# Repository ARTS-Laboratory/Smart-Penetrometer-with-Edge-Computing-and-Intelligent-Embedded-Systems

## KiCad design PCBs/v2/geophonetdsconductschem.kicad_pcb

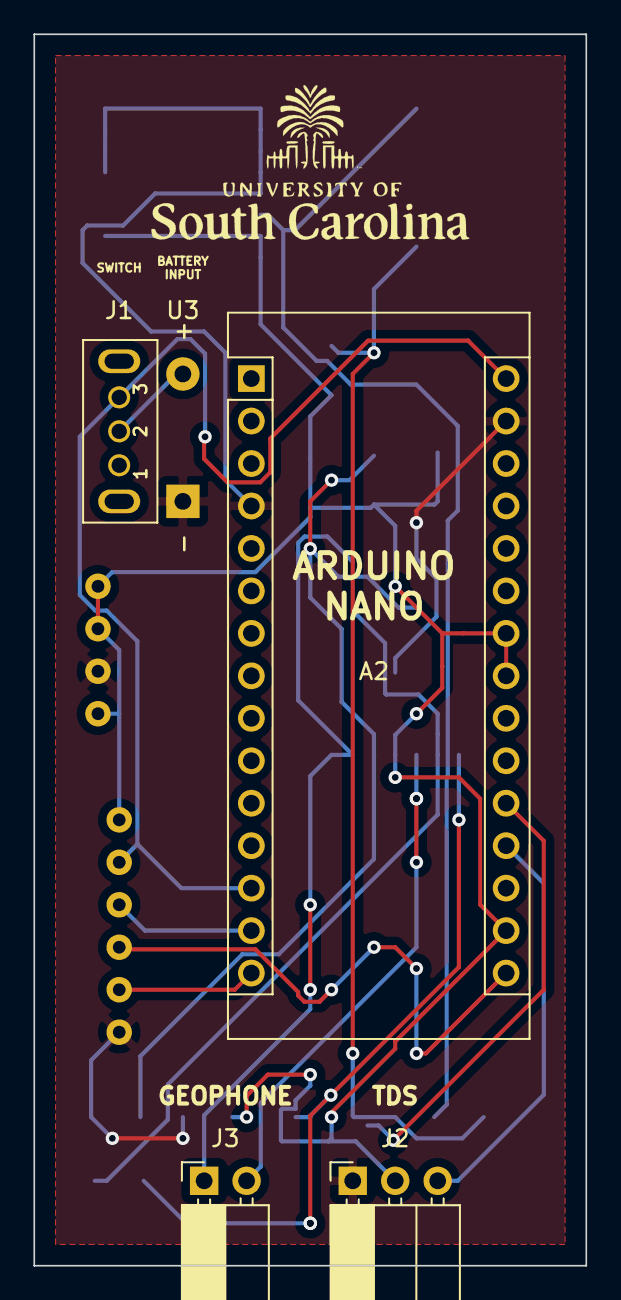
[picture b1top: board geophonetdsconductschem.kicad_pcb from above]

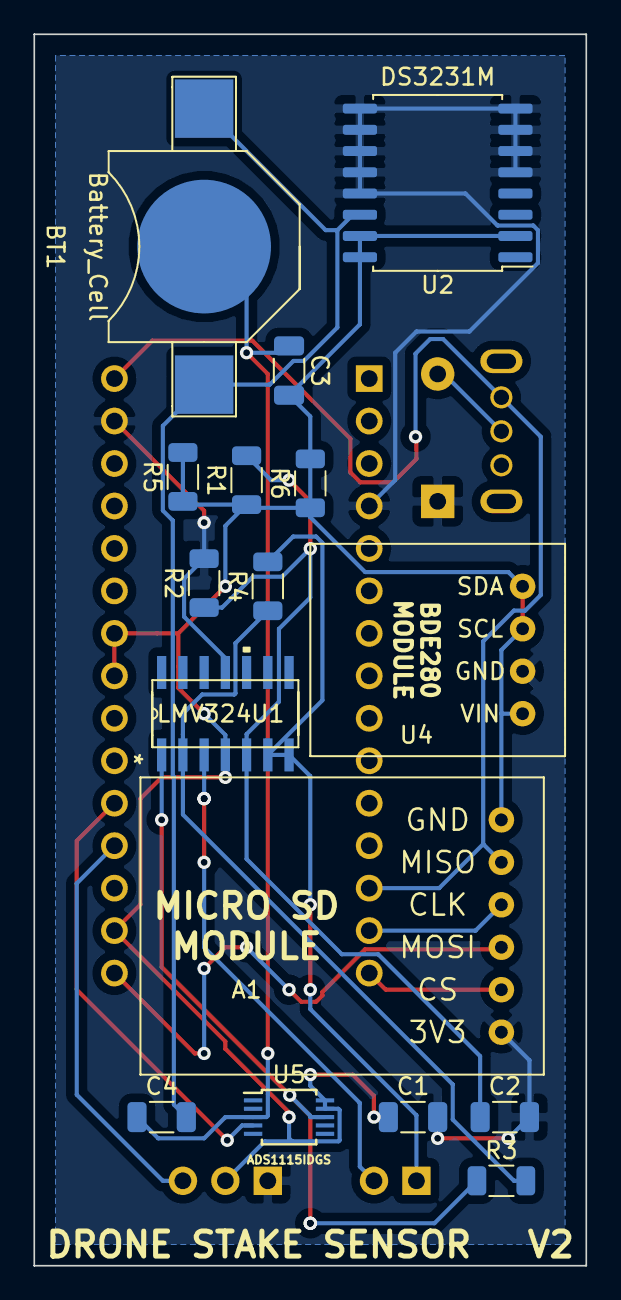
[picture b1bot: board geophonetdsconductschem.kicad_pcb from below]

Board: 2 copper layers, 33.0 x 73.7 mm, 21 parts (16 on the bottom side), 16 nets.

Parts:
A1: SD_Card_Module; SD Module
A2: Arduino_Nano_v3.x; Arduino_Nano
BT1: Battery_Cell; battery_holder_10mm
C1, C2, C3, C4: C_Small; C_1206_3216Metric
J1: XLR3_Switched; grounded_switch
J2: Conn_01x03_Female; PinSocket_1x03_P2.54mm_Horizontal
J3: Conn_01x02_Female; PinSocket_1x02_P2.54mm_Horizontal
R1, R2, R3, R4, R5, R6: R_Small_US; R_1206_3216Metric
U1: LMV324; LMV324IDR
U2: DS3231M; SOIC-16W_7.5x10.3mm_P1.27mm
U3: Battery_Input
U4: 4023; TDS_module
U5: ADS1115IDGS; TSSOP-10_3x3mm_P0.5mm

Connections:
GND: A1.6, A2.4, A2.29, C1.2, C2.2, J2.1, R2.2, U1.11, U2.5, U2.6, U2.7, U2.8, U2.9, U2.10, U2.11, U2.12, U2.13, U3.2, U4.10
GNDS: BT1.2, C3.1, C4.1, U5.3
unnamed: A1.1, A2.17, A2.23, A2.24, C1.1, C3.2, J2.2, R1.1, R5.1, R5.2, R6.1, R6.2, U1.4, U2.2, U2.15, U2.16, U4.11, U4.12, U4.13, U5.9, U5.10
unnamed: A1.2, A2.13, A2.30, J1.3
unnamed: A1.3, A2.14
unnamed: A1.4, A2.16
unnamed: A1.5, A2.15
unnamed: A2.19, J2.3
unnamed: A2.20, U5.4
unnamed: BT1.1, C4.2, U2.14
unnamed: C2.1, R1.2, R2.1, U1.5
unnamed: J3.1, R4.2, U1.6, U1.7
unnamed: J3.2, U1.3
unnamed: R3.1, U1.1, U5.8
unnamed: R3.2, R4.1, U1.2
VCC: J1.2, U3.1

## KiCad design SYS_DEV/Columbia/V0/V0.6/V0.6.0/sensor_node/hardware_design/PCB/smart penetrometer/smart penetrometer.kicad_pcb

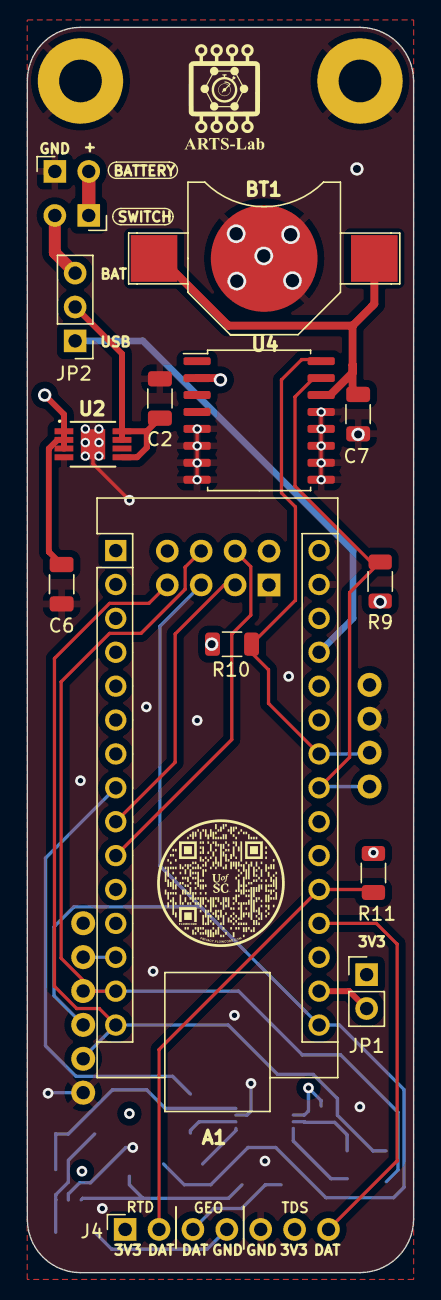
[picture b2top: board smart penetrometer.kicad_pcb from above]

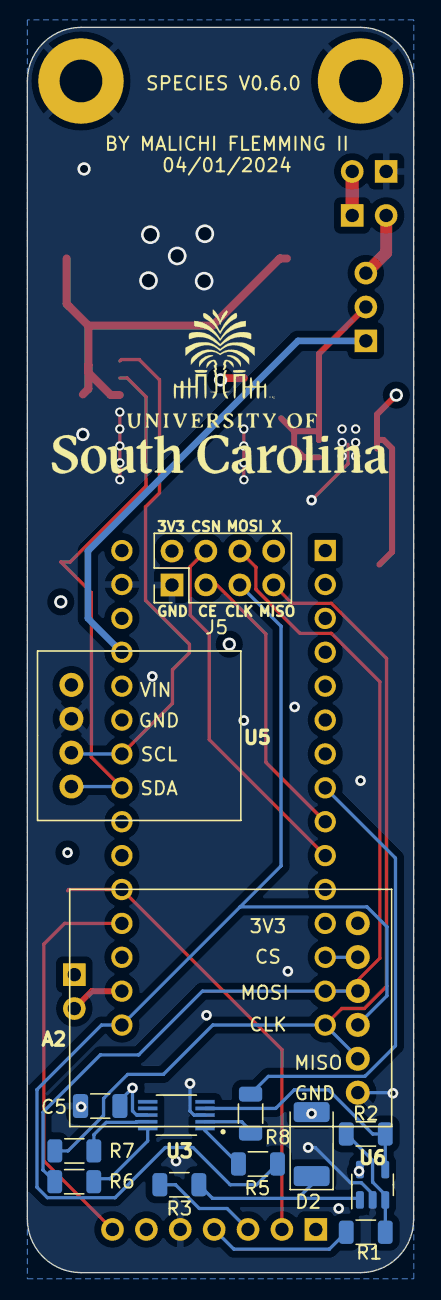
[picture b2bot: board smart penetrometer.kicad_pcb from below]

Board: 4 copper layers, 29.0 x 93.3 mm, 31 parts (13 on the bottom side), 28 nets.

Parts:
A1: Arduino Nano; Arduino_Nano
A2: SD_Card_Module; SD Module
BT1: Battery_Cell; battery_holder_10mm
C2, C6: C_1uF; C_1206_3216Metric
C5, C7: C_0.1uF; C_1206_3216Metric
D2: SMZ1_770mV; D_MELF
H1, H2: MountingHole_Pad; MountingHole_3.2mm_M3_Pad
J2, J3: Conn_01x02; PinSocket_1x02_P2.54mm_Horizontal
J4: Conn_01x07_Female; PinSocket_1x07_P2.54mm_Horizontal
J5: Conn_02x04; PinSocket_2x04_P2.54mm_Vertical
JP1: Jumper_2; PinHeader_1x02_P2.54mm_Vertical
JP2: Jumper_3; PinHeader_1x03_P2.54mm_Vertical
R1: R_7.5K; R_1206_3216Metric
R2: R_32k; R_1206_3216Metric
R3: R_100; R_1206_3216Metric
R5, R6, R7, R8: R_50; R_1206_3216Metric
R9, R10: R_1kOhm; R_1206_3216Metric
R11: R_10K; R_1206_3216Metric
U2: ADP124ARHZ-3.3-R7; RH_8_1_ADI
U3: ADS1118IDGS; ADS1118_10VSSOP
U4: DS3231M; SOIC-16W_7.5x10.3mm_P1.27mm
U5: BME260
U6: LM321; SOT-23-5

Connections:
3V3: A1.18 (AREF), A2.1 (3V3), C5.1, C6.1, J4.1, J4.6, J5.2, JP1.1 (A), R9.1, R10.1, U2.1 (VOUT), U2.2 (VOUT), U2.3 (VOUTSENSE), U3.8 (VDD), U4.2 (VCC), U5.13, U6.5 (V+)
5V0: A1.27 (+5V), JP2.1 (A)
+BATT: J2.2, J3.1
BATT: J3.2, JP2.3 (B)
CE: A1.9 (D6), J5.3
CLK: A1.16 (D13), A2.4 (CLK), J5.5, R5.1
CSN: A1.10 (D7), J5.4
EC_DATA: A1.19 (A0), J4.7
GEOPHONE: J4.3, R3.1
GEO_CS: A1.8 (D5), R8.1
GND: A1.29 (GND), A2.6 (GND), BT1.2 (-), C2.2, C5.2, C6.2, C7.1, H1.1, H2.1, J2.1, J4.5, J5.1, U2.4 (GND), U2.EPAD, U3.3 (GND), U4.5 (GND), U4.6 (GND), U4.7 (GND), U4.8 (GND), U4.9 (GND), U4.10 (GND), U4.11 (GND), U4.12 (GND), U4.13 (GND), U5.10, U6.2 (V-)
GNDA: A1.4 (GND), D2.2 (A), J4.4, R1.2, R11.2
MISO: A1.15 (D12), A2.5 (MISO), J5.7, R7.1
MOSI: A1.14 (D11), A2.3 (MOSI), J5.6, R6.1
unnamed: A1.17 (3V3), JP1.2 (B)
unnamed: BT1.1 (+), C7.2, U4.14 (VBAT)
unnamed: D2.1 (K), R3.2, U6.1 (+)
unnamed: C2.1, JP2.2 (C), U2.5 (EN), U2.7 (VIN), U2.8 (VIN)
unnamed: R2.1, U3.4 (AIN0), U6.4
unnamed: R6.2, U3.10 (DIN)
unnamed: R7.2, U3.9 (DOUT/~DRDY)
unnamed: R5.2, U3.1 (SCLK)
unnamed: R8.2, U3.2 (~CS)
unnamed: R1.1, R2.2, U6.3 (-)
RTD: A1.20 (A1), J4.2, R11.1
SCL: A1.24 (A5), R10.2, U4.16 (SCL), U5.11
SDA: A1.23 (A4), R9.2, U4.15 (SDA), U5.12
SD_CS: A1.13 (D10), A2.2 (CS)

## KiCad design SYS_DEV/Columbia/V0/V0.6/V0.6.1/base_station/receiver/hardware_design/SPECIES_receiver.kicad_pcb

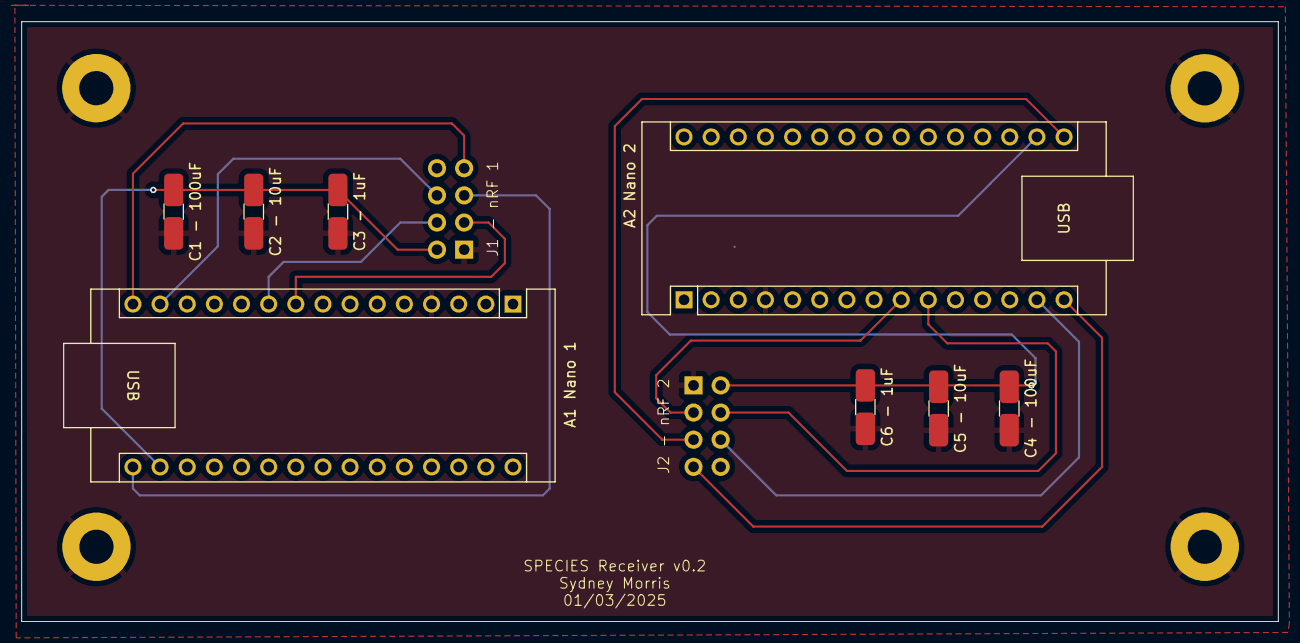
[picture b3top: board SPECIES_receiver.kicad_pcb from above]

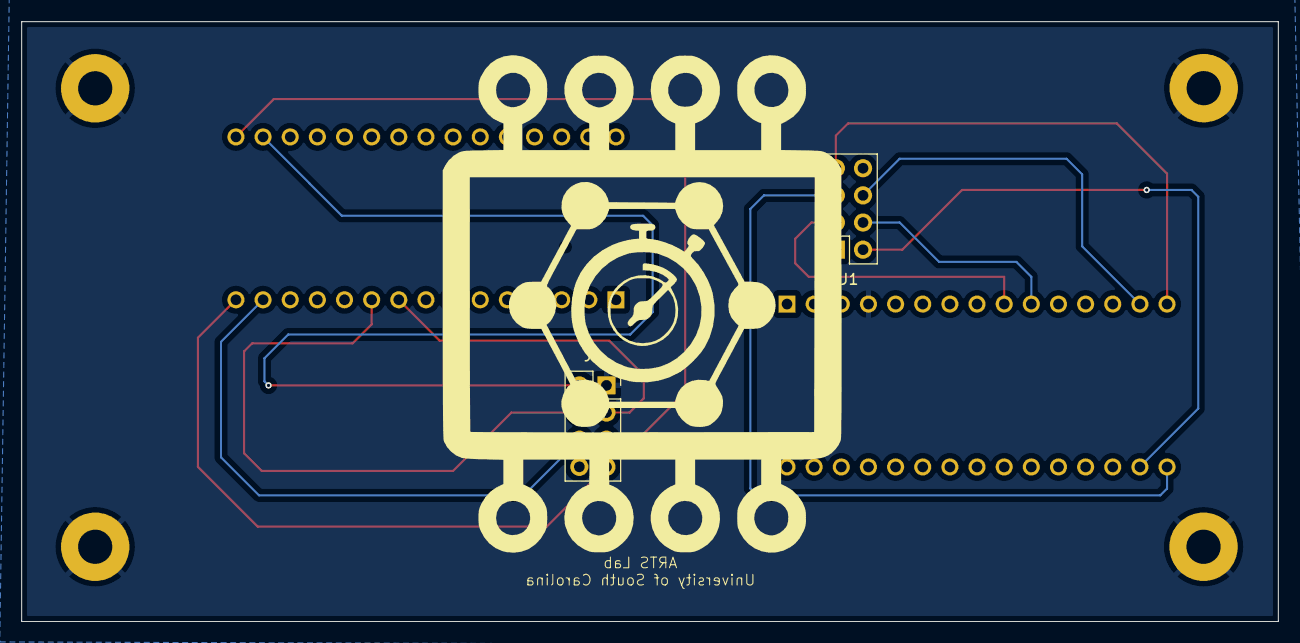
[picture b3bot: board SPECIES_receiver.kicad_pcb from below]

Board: 2 copper layers, 117.6 x 56.1 mm, 10 parts (2 on the bottom side), 8 nets.

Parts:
A1: Nano 1; Arduino_Nano
A2: Nano 2; Arduino_Nano
C1 - 100uF, C2 - 10uF, C3 - 1uF, C4 - 100uF, C5 - 10uF, C6 - 1uF: C_Small; C_1206_3216Metric
J1, J2: Conn_02x04_Odd_Even_MountingPin; PinSocket_2x04_P2.54mm_Vertical

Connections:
3V3: A1.17 (3V3), A2.17 (3V3), C1 - 100uF.1, C2 - 10uF.1, C3 - 1uF.1, C4 - 100uF.1, C5 - 10uF.1, C6 - 1uF.1, J1.2, J2.2
CE: A1.9 (D6), A2.9 (D6), J1.3, J2.3
CLK: A1.16 (D13), A2.16 (D13), J1.5, J2.5
CSN: A1.10 (D7), A2.10 (D7), J1.4, J2.4
GND: A1.4 (GND), A2.4 (GND), C1 - 100uF.2, C2 - 10uF.2, C3 - 1uF.2, C4 - 100uF.2, C5 - 10uF.2, C6 - 1uF.2, J1.1, J2.1
MISO: A1.15 (D12), A2.15 (D12), J1.7, J2.7
MOSI: A1.14 (D11), A2.14 (D11), J1.6, J2.6
unnamed: A2.27 (+5V), A2.30 (VIN)

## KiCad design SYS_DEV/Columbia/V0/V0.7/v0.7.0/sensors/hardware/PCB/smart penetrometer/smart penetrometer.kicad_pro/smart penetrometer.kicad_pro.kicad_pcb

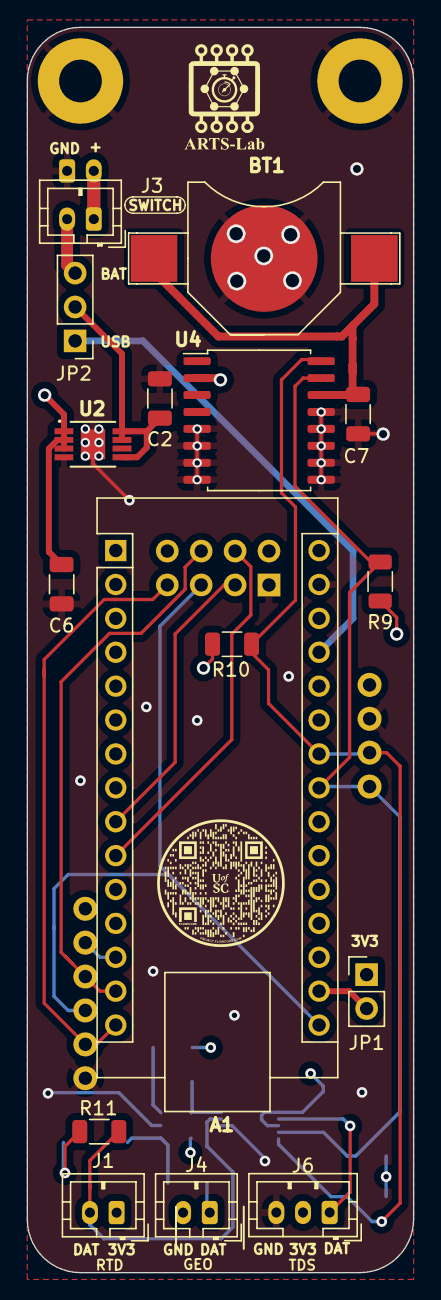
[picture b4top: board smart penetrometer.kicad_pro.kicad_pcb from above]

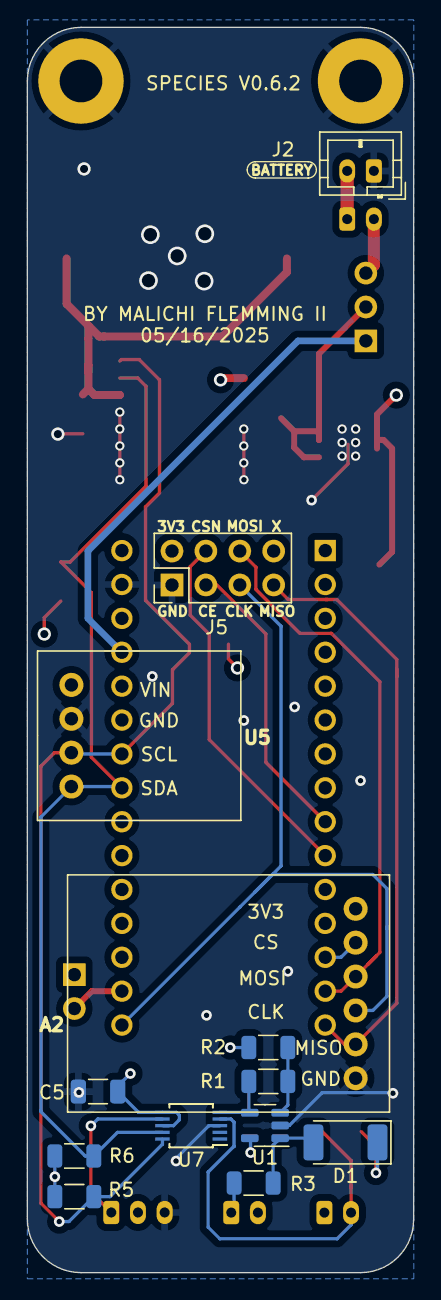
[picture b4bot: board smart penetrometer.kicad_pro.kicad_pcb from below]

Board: 4 copper layers, 29.0 x 93.3 mm, 31 parts (12 on the bottom side), 23 nets.

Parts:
A1: Arduino Nano; Arduino_Nano
A2: SD_Card_Module; SD Module
BT1: Battery_Cell; battery_holder_10mm
C2, C6: C_1uF; C_1206_3216Metric
C5, C7: C_0.1uF; C_1206_3216Metric
D1: SMZ1_770mV; D_MELF
H1, H2: MountingHole_Pad; MountingHole_3.2mm_M3_Pad
J1: RTD; JST_PH_B2B-PH-K_1x02_P2.00mm_Vertical
J2, J3: Conn_01x02; JST_PH_B2B-PH-K_1x02_P2.00mm_Vertical
J4: GEO; JST_PH_B2B-PH-K_1x02_P2.00mm_Vertical
J5: Conn_02x04; PinSocket_2x04_P2.54mm_Vertical
J6: EC; JST_PH_B3B-PH-K_1x03_P2.00mm_Vertical
JP1: Jumper_2; PinHeader_1x02_P2.54mm_Vertical
JP2: Jumper_3; PinHeader_1x03_P2.54mm_Vertical
R1: R_32K; R_1206_3216Metric
R2: R_7.5K; R_1206_3216Metric
R3: R_100; R_1206_3216Metric
R5, R6, R11: R_10K; R_1206_3216Metric
R9, R10: R_1kOhm; R_1206_3216Metric
U1: LM321; SOT-23-5
U2: ADP124ARHZ-3.3-R7; RH_8_1_ADI
U4: DS3231M; SOIC-16W_7.5x10.3mm_P1.27mm
U5: BME260
U7: ADS1115IDGS; TSSOP-10_3x3mm_P0.5mm

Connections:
3V3: A1.18 (AREF), A2.1 (3V3), C5.1, C6.1, J1.1, J5.2, J6.2, JP1.1 (A), R5.1, R6.1, R9.1, R10.1, U1.5 (V+), U2.1 (VOUT), U2.2 (VOUT), U2.3 (VOUTSENSE), U4.2 (VCC), U5.13, U7.6 (AIN2), U7.8 (VDD)
5V0: A1.27 (+5V), JP2.1 (A)
+BATT: J2.2, J3.1
BATT: J3.2, JP2.3 (B)
CE: A1.9 (D6), J5.3
CLK: A1.16 (D13), A2.4 (CLK), J5.5
CSN: A1.10 (D7), J5.4
EC_DATA: J6.1, U7.7 (AIN3)
GEOPHONE: J4.1, R3.1
GND: A1.29 (GND), A2.6 (GND), BT1.2 (-), C2.2, C5.2, C6.2, C7.1, H1.1, H2.1, J2.1, J5.1, J6.3, U1.2 (V-), U2.4 (GND), U2.EPAD, U4.5 (GND), U4.6 (GND), U4.7 (GND), U4.8 (GND), U4.9 (GND), U4.10 (GND), U4.11 (GND), U4.12 (GND), U4.13 (GND), U5.10, U7.3 (GND)
GNDA: A1.4 (GND), D1.1 (K), J4.2, R2.2, R11.2
MISO: A1.15 (D12), A2.5 (MISO), J5.7
MOSI: A1.14 (D11), A2.3 (MOSI), J5.6
unnamed: A1.17 (3V3), JP1.2 (B)
unnamed: BT1.1 (+), C7.2, U4.14 (VBAT)
unnamed: D1.2 (A), R3.2, U1.1 (+)
unnamed: C2.1, JP2.2 (C), U2.5 (EN), U2.7 (VIN), U2.8 (VIN)
unnamed: R1.2, R2.1, U1.3 (-)
unnamed: R1.1, U1.4, U7.5 (AIN1)
RTD: J1.2, R11.1, U7.4 (AIN0)
SCL: A1.24 (A5), R5.2, R10.2, U4.16 (SCL), U5.11, U7.10 (SCL)
SDA: A1.23 (A4), R6.2, R9.2, U4.15 (SDA), U5.12, U7.9 (SDA)
SD_CS: A1.13 (D10), A2.2 (CS)

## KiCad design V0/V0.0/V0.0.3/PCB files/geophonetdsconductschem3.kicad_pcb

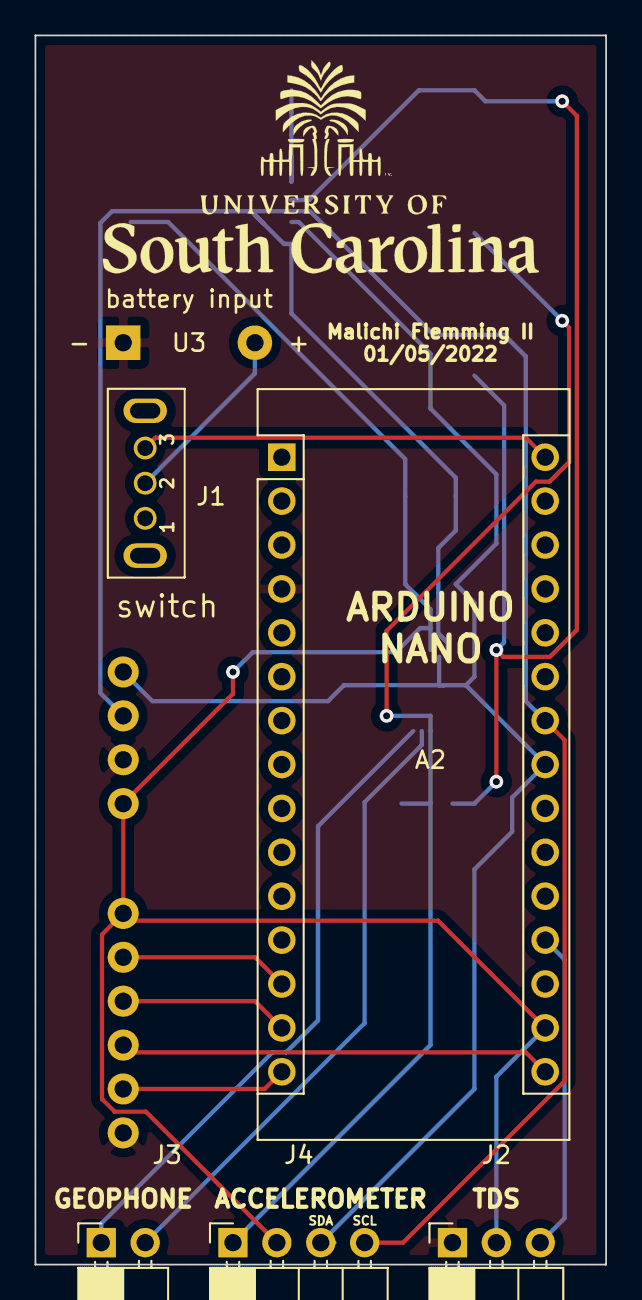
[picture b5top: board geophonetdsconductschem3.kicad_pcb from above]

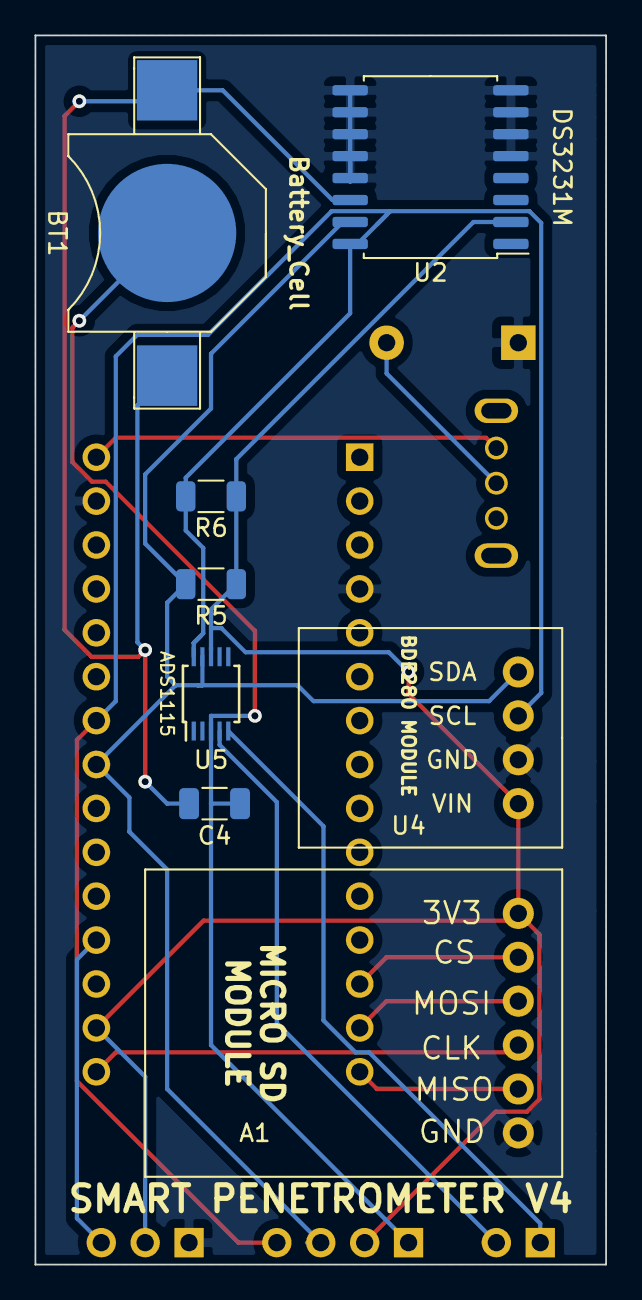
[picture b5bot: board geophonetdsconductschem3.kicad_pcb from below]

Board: 2 copper layers, 33.0 x 71.1 mm, 15 parts (8 on the bottom side), 15 nets.

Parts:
A1: SD_Card_Module; SD Module
A2: Arduino_Nano_v3.x; Arduino_Nano
BT1: Battery_Cell; battery_holder_10mm
C4: C_Small; C_1206_3216Metric
J1: XLR3_Switched; grounded_switch
J2: Conn_01x03_Female; PinSocket_1x03_P2.54mm_Horizontal
J3: Conn_01x02_Female; PinSocket_1x02_P2.54mm_Horizontal
J4: Conn_01x04_Female; PinSocket_1x04_P2.54mm_Horizontal
R5, R6: R_Small_US; R_1206_3216Metric
U1: 4001; uofsc_logo_1in
U2: DS3231M; SOIC-16W_7.5x10.3mm_P1.27mm
U3: Battery_Input
U4: 4023; TDS_module
U5: ADS1115IDGS; TSSOP-10_3x3mm_P0.5mm

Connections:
GND: A1.6, A2.4, A2.29, J2.1, U2.5, U2.6, U2.7, U2.8, U2.9, U2.10, U2.11, U2.12, U2.13, U3.2, U4.10
GNDS: BT1.2, C4.1, J4.1, U5.3
unnamed: A1.1, A2.17, J2.2, J4.2, R5.1, R6.1, U2.2, U4.13, U5.8
unnamed: A1.2, A2.13
unnamed: A1.3, A2.14
unnamed: A1.4, A2.16
unnamed: A1.5, A2.15
unnamed: A2.19, J2.3
unnamed: A2.23, J4.3, R5.2, U2.15, U4.12, U5.9
unnamed: A2.24, J4.4, R6.2, U2.16, U4.11, U5.10
unnamed: A2.30, J1.3
unnamed: BT1.1, C4.2, U2.14
unnamed: J3.1, U5.5
unnamed: J3.2, U5.4
VCC: J1.2, U3.1

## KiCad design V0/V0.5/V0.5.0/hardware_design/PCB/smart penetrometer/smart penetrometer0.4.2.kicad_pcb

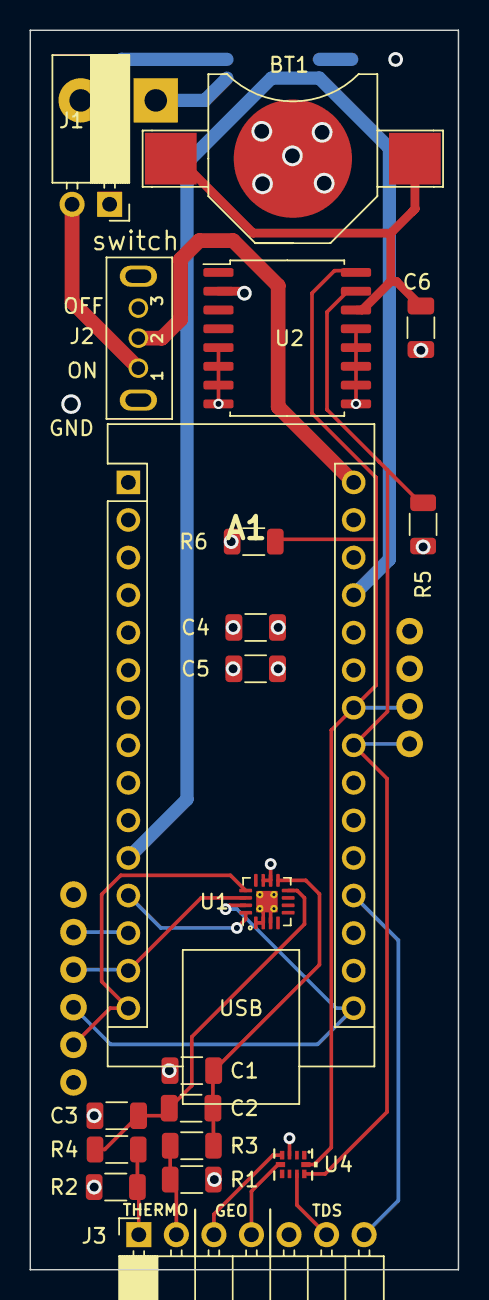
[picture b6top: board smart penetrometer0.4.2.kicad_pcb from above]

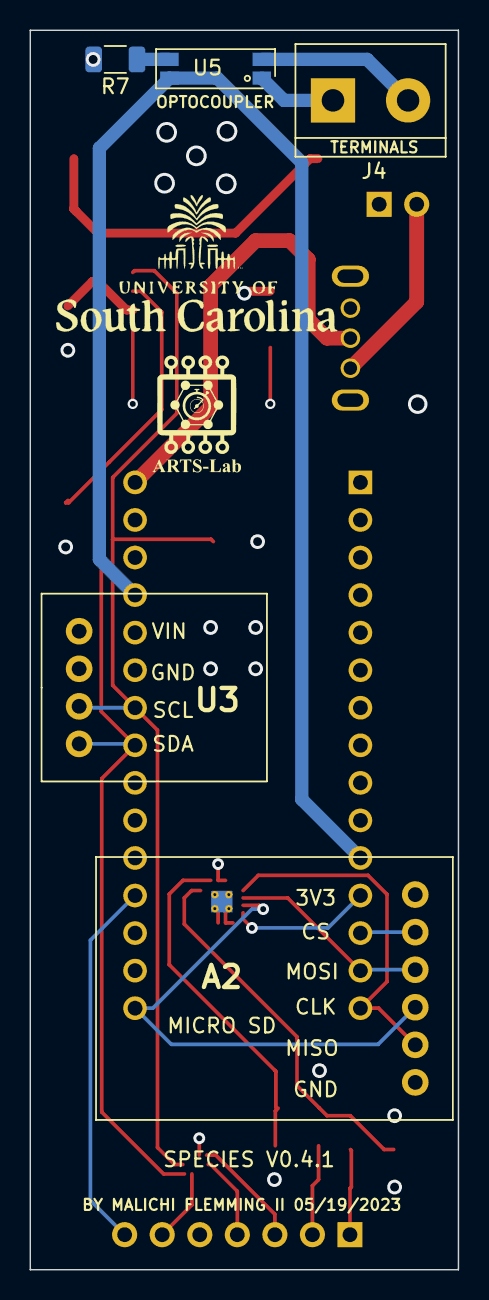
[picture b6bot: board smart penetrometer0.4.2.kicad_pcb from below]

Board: 4 copper layers, 29.0 x 83.8 mm, 25 parts (5 on the bottom side), 23 nets.

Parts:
A1: Arduino_Nano_v3.x; Arduino_Nano
A2: SD_Card_Module; SD Module
BT1: Battery_Cell; battery_holder_10mm
C1, C3: C_0.047uF; C_1206_3216Metric
C2: C_0.47uF; C_1206_3216Metric
C4, C5: C_0.1uF; C_1206_3216Metric
C6: C_Small; C_1206_3216Metric
J1: Conn_01x02_Female; PinSocket_1x02_P2.54mm_Horizontal
J2: XLR3_Switched; grounded_switch
J3: Conn_01x07_Female; PinSocket_1x07_P2.54mm_Horizontal
J4: Screw_Terminal; TerminalBlock_bornier-2_P5.08mm
R1, R2: R_1MOhm; R_1206_3216Metric
R3, R4: R_800Ohm; R_1206_3216Metric
R5, R6: R_Small_US; R_1206_3216Metric
R7: R_1.9kOhm; R_1206_3216Metric
U1: ADS1120-PW; VQFN-16-1EP_3x3mm_P0.5mm_EP1.45x1.45mm_ThermalVias
U2: DS3231M; SOIC-16W_7.5x10.3mm_P1.27mm
U3: 4023; TDS_module
U4: ADS1115IDGS; 10X2QFN
U5: VO615A; Vishay_VOS615A

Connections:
3V3: A1.17 (3V3), A2.1 (3V3), C4.1, C5.1, J3.6, R1.1, R5.1, R6.1, U1.10 (AVDD), U1.11 (DVDD), U2.2 (VCC), U3.13, U4.8 (VDD)
5V0: A1.11 (D8), A1.27 (+5V), U5.4
CLK: A1.16 (D13), A2.4 (CLK), U1.15 (SCLK)
EC_DATA: A1.19 (A0), J3.7
GEO_AMP_0: J3.3, U4.4 (AIN0)
GEO_AMP_1: J3.4, U4.5 (AIN1)
GND: A1.4 (GND), A1.29 (GND), A2.6 (GND), BT1.2 (-), C1.1, C3.2, C4.2, C5.2, C6.1, J1.1, J3.5, R2.2, R7.2, U1.1 (CLK), U1.2 (DGND), U1.3 (AVSS), U1.17 (thermal), U2.5 (GND), U2.6 (GND), U2.7 (GND), U2.8 (GND), U2.9 (GND), U2.10 (GND), U2.11 (GND), U2.12 (GND), U2.13 (GND), U3.10, U4.3 (GND)
MISO: A1.15 (D12), A2.5 (MISO), U1.13 (DOUT/~DRDY)
MOSI: A1.14 (D11), A2.3 (MOSI), U1.14 (DIN)
unnamed: BT1.1 (+), C6.2, U2.14 (VBAT)
unnamed: C1.2, C2.1, R3.1, U1.9 (AIN0/REFP1)
unnamed: C2.2, C3.1, R4.1, U1.8 (AIN1)
unnamed: J4.1, U5.1
unnamed: J4.2, U5.2
unnamed: R7.1, U5.3
POWER: J1.2, J2.1
SCL: A1.24 (A5), R6.2, U2.16 (SCL), U3.11, U4.10 (SCL)
SDA: A1.23 (A4), R5.2, U2.15 (SDA), U3.12, U4.9 (SDA)
SD_CS: A1.13 (D10), A2.2 (CS)
TEMP_AMP_0: J3.2, R1.2, R3.2
TEMP_AMP_1: J3.1, R2.1, R4.2
TEMP_AMP_CS: A1.12 (D9), U1.16 (~CS)
VIN: A1.30 (VIN), J2.2

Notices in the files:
parts and their libraries:
Copyright 2021 Accelerated Designs. All rights reserved.
